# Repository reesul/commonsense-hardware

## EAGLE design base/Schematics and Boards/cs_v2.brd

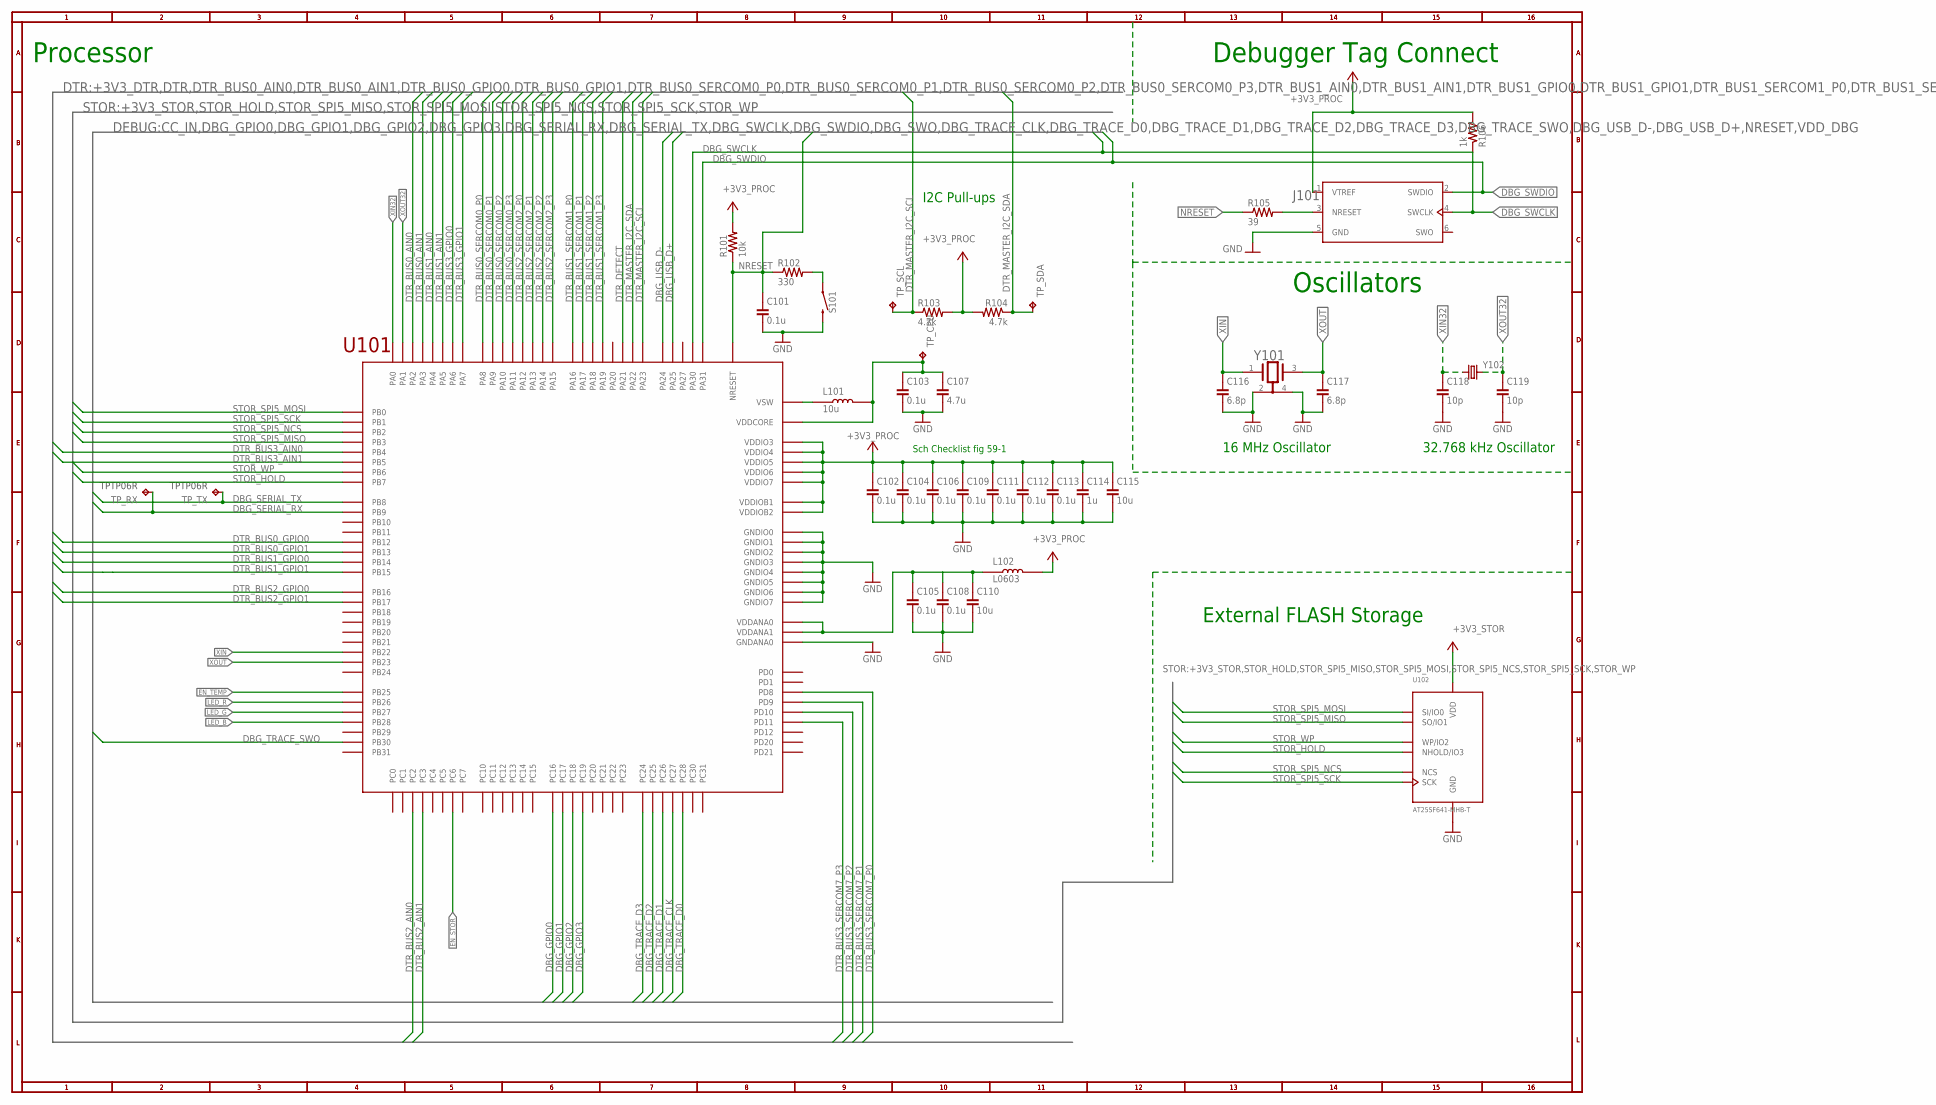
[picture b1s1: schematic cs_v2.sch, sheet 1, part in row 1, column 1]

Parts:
C101, C102, C103, C104, C105, C106, C108, C109, C111, C112, C113: 0.1u; C0402; VOLTAGE 10V; PART_NO C0402C104K8RACTU
C107: 4.7u; C0805; VOLTAGE 10V; PART_NO C0805C475K8RACTU
C110, C115: 10u; C0805; VOLTAGE 10V; PART_NO C0805C106M8RACTU
C114: 1u; C0402; VOLTAGE 10V; PART_NO C0402C105M8PACTU
C116, C117: 6.8p; C0402; PART_NO C0402C689D8GAC7867
C118, C119: 10p; C0402; PART_NO C0402C100C8GACTU
J101: J-JTAG-CORTEX-NEEDLE6; 8.06.16_6-PIN_NEEDLE_ADAPTER_NO-LEGS
L101: 10u; IND_LQH3NPN; PART_NO LQH3NPN100NM0L
L102: L0603; PART_NO BLM18PG471SN1D
R101: 10k; R0402; PART_NO P10KJCT-ND
R102: 330; R0402; PART_NO ERJ-2GEJ331X
R103, R104: 4.7k; R0402; PART_NO ERJ-3GEYJ472V
R105: 39; R0402; PART_NO ERJ-2GEJ390X
R106: 1k; R0402; PART_NO ERJ-2GEJ102X
S101: SW_EVQ-P7L01P_SPST_RA; SW_EVQ-P7L01P
TP_CPU: TPTP06R; TP06R
TP_RX: TPTP06R; TP06R
TP_SCL: TPTP06R; TP06R
TP_SDA: TPTP06R; TP06R
TP_TX: TPTP06R; TP06R
U101: ATSAMD51; TFBGA120
U102: AT25SF641-MHB-T; 8-UDFN
Y101: 16M; XTAL_EPSON_TSX3225
Y102: ABS07-32.768KHZ-9-T; XTAL320X150X90

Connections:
+3V3_PROC: C102.1, C104.1, C106.1, C109.1, C111.1, C112.1, C113.1, C114.1, C115.1, J101.1 (VTREF), L102.2, R101.2, R103.2, R104.2, R106.2, U101.VDDIO3, U101.VDDIO4, U101.VDDIO5, U101.VDDIO6, U101.VDDIO7, U101.VDDIOB1, U101.VDDIOB2; also elsewhere on the board
+3V3_STOR: U102.8 (VDD); also elsewhere on the board
DBG_GPIO0: U101.PC16; also elsewhere on the board
DBG_GPIO1: U101.PC17; also elsewhere on the board
DBG_GPIO2: U101.PC18; also elsewhere on the board
DBG_GPIO3: U101.PC19; also elsewhere on the board
DBG_SERIAL_RX: TP_RX.TP, U101.PB09 (PB9); also elsewhere on the board
DBG_SERIAL_TX: TP_TX.TP, U101.PB08 (PB8); also elsewhere on the board
DBG_SWCLK: J101.4 (SWCLK), R106.1, U101.PA30; also elsewhere on the board
DBG_SWDIO: J101.2 (SWDIO), U101.PA31; also elsewhere on the board
DBG_TRACE_CLK: U101.PC27; also elsewhere on the board
DBG_TRACE_D0: U101.PC28; also elsewhere on the board
DBG_TRACE_D1: U101.PC26; also elsewhere on the board
DBG_TRACE_D2: U101.PC25; also elsewhere on the board
DBG_TRACE_D3: U101.PC24; also elsewhere on the board
DBG_TRACE_SWO: U101.PB30; also elsewhere on the board
DBG_USB_D+: U101.PA25; also elsewhere on the board
DBG_USB_D-: U101.PA24; also elsewhere on the board
DTR_BUS0_AIN0: U101.PA02 (PA2); also elsewhere on the board
DTR_BUS0_AIN1: U101.PA03 (PA3); also elsewhere on the board
DTR_BUS0_GPIO0: U101.PB12; also elsewhere on the board
DTR_BUS0_GPIO1: U101.PB13; also elsewhere on the board
DTR_BUS0_SERCOM0_P0: U101.PA08 (PA8); also elsewhere on the board
DTR_BUS0_SERCOM0_P1: U101.PA09 (PA9); also elsewhere on the board
DTR_BUS0_SERCOM0_P2: U101.PA10; also elsewhere on the board
DTR_BUS0_SERCOM0_P3: U101.PA11; also elsewhere on the board
DTR_BUS1_AIN0: U101.PA04 (PA4); also elsewhere on the board
DTR_BUS1_AIN1: U101.PA05 (PA5); also elsewhere on the board
DTR_BUS1_GPIO0: U101.PB14; also elsewhere on the board
DTR_BUS1_GPIO1: U101.PB15; also elsewhere on the board
DTR_BUS1_SERCOM1_P0: U101.PA16; also elsewhere on the board
DTR_BUS1_SERCOM1_P1: U101.PA17; also elsewhere on the board
DTR_BUS1_SERCOM1_P2: U101.PA18; also elsewhere on the board
DTR_BUS1_SERCOM1_P3: U101.PA19; also elsewhere on the board
DTR_BUS2_AIN0: U101.PC02 (PC2); also elsewhere on the board
DTR_BUS2_AIN1: U101.PC03 (PC3); also elsewhere on the board
DTR_BUS2_GPIO0: U101.PB16; also elsewhere on the board
DTR_BUS2_GPIO1: U101.PB17; also elsewhere on the board
DTR_BUS2_SERCOM2_P0: U101.PA12; also elsewhere on the board
DTR_BUS2_SERCOM2_P1: U101.PA13; also elsewhere on the board
DTR_BUS2_SERCOM2_P2: U101.PA14; also elsewhere on the board
DTR_BUS2_SERCOM2_P3: U101.PA15; also elsewhere on the board
DTR_BUS3_AIN0: U101.PB04 (PB4); also elsewhere on the board
DTR_BUS3_AIN1: U101.PB05 (PB5); also elsewhere on the board
DTR_BUS3_GPIO0: U101.PA06 (PA6); also elsewhere on the board
DTR_BUS3_GPIO1: U101.PA07 (PA7); also elsewhere on the board
DTR_BUS3_SERCOM7_P0: U101.PD08 (PD8); also elsewhere on the board
DTR_BUS3_SERCOM7_P1: U101.PD09 (PD9); also elsewhere on the board
DTR_BUS3_SERCOM7_P2: U101.PD10; also elsewhere on the board
DTR_BUS3_SERCOM7_P3: U101.PD11; also elsewhere on the board
DTR_DETECT: U101.PA21; also elsewhere on the board
DTR_MASTER_I2C_SCL: R103.1, TP_SCL.TP, U101.PA23; also elsewhere on the board
DTR_MASTER_I2C_SDA: R104.1, TP_SDA.TP, U101.PA22; also elsewhere on the board
EN_STOR: U101.PC06 (PC6); also elsewhere on the board
EN_TEMP: U101.PB25; also elsewhere on the board
GND: C101.2, C102.2, C103.2, C104.2, C105.2, C106.2, C107.2, C108.2, C109.2, C110.2, C111.2, C112.2, C113.2, C114.2, C115.2, C116.2, C117.2, C118.2, C119.2, J101.5 (GND), S101.2_1 (2), S101.2_2 (2), U101.GNDANA0, U101.GNDIO0, U101.GNDIO1, U101.GNDIO2, U101.GNDIO3, U101.GNDIO4, U101.GNDIO5, U101.GNDIO6, U101.GNDIO7, U102.4 (GND), U102.9 (GND), Y101.2 (1_GND), Y101.4 (2_GND); also elsewhere on the board
JTAG_NRESET: J101.3 (NRESET), R105.2
LED_B: U101.PB28; also elsewhere on the board
LED_G: U101.PB27; also elsewhere on the board
LED_R: U101.PB26; also elsewhere on the board
unnamed: R102.2, S101.1_1 (1), S101.1_2 (1)
NRESET: C101.1, R101.1, R102.1, R105.1, U101.NRESET; also elsewhere on the board
STOR_HOLD: U101.PB07 (PB7), U102.7 (NHOLD/IO3)
STOR_SPI5_MISO: U101.PB03 (PB3), U102.2 (SO/IO1)
STOR_SPI5_MOSI: U101.PB00 (PB0), U102.5 (SI/IO0)
STOR_SPI5_NCS: U101.PB02 (PB2), U102.1 (NCS)
STOR_SPI5_SCK: U101.PB01 (PB1), U102.6 (SCK)
STOR_WP: U101.PB06 (PB6), U102.3 (WP/IO2)
VDDANA: C105.1, C108.1, C110.1, L102.1, U101.VDDANA0, U101.VDDANA1
VDDCORE: C103.1, C107.1, L101.2, L101.P$2, TP_CPU.TP, U101.VDDCORE
VSW: L101.1, L101.P$1, U101.VSW
XIN: C116.1, U101.PB22, Y101.1
XIN32: C118.1, U101.PA00 (PA0), Y102.1
XOUT: C117.1, U101.PB23, Y101.3
XOUT32: C119.1, U101.PA01 (PA1), Y102.2

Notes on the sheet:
Sch Checklist fig 59-1
Oscillators
16 MHz Oscillator
32.768 kHz Oscillator
Processor
Debugger Tag Connect
I2C Pull-ups
External FLASH Storage

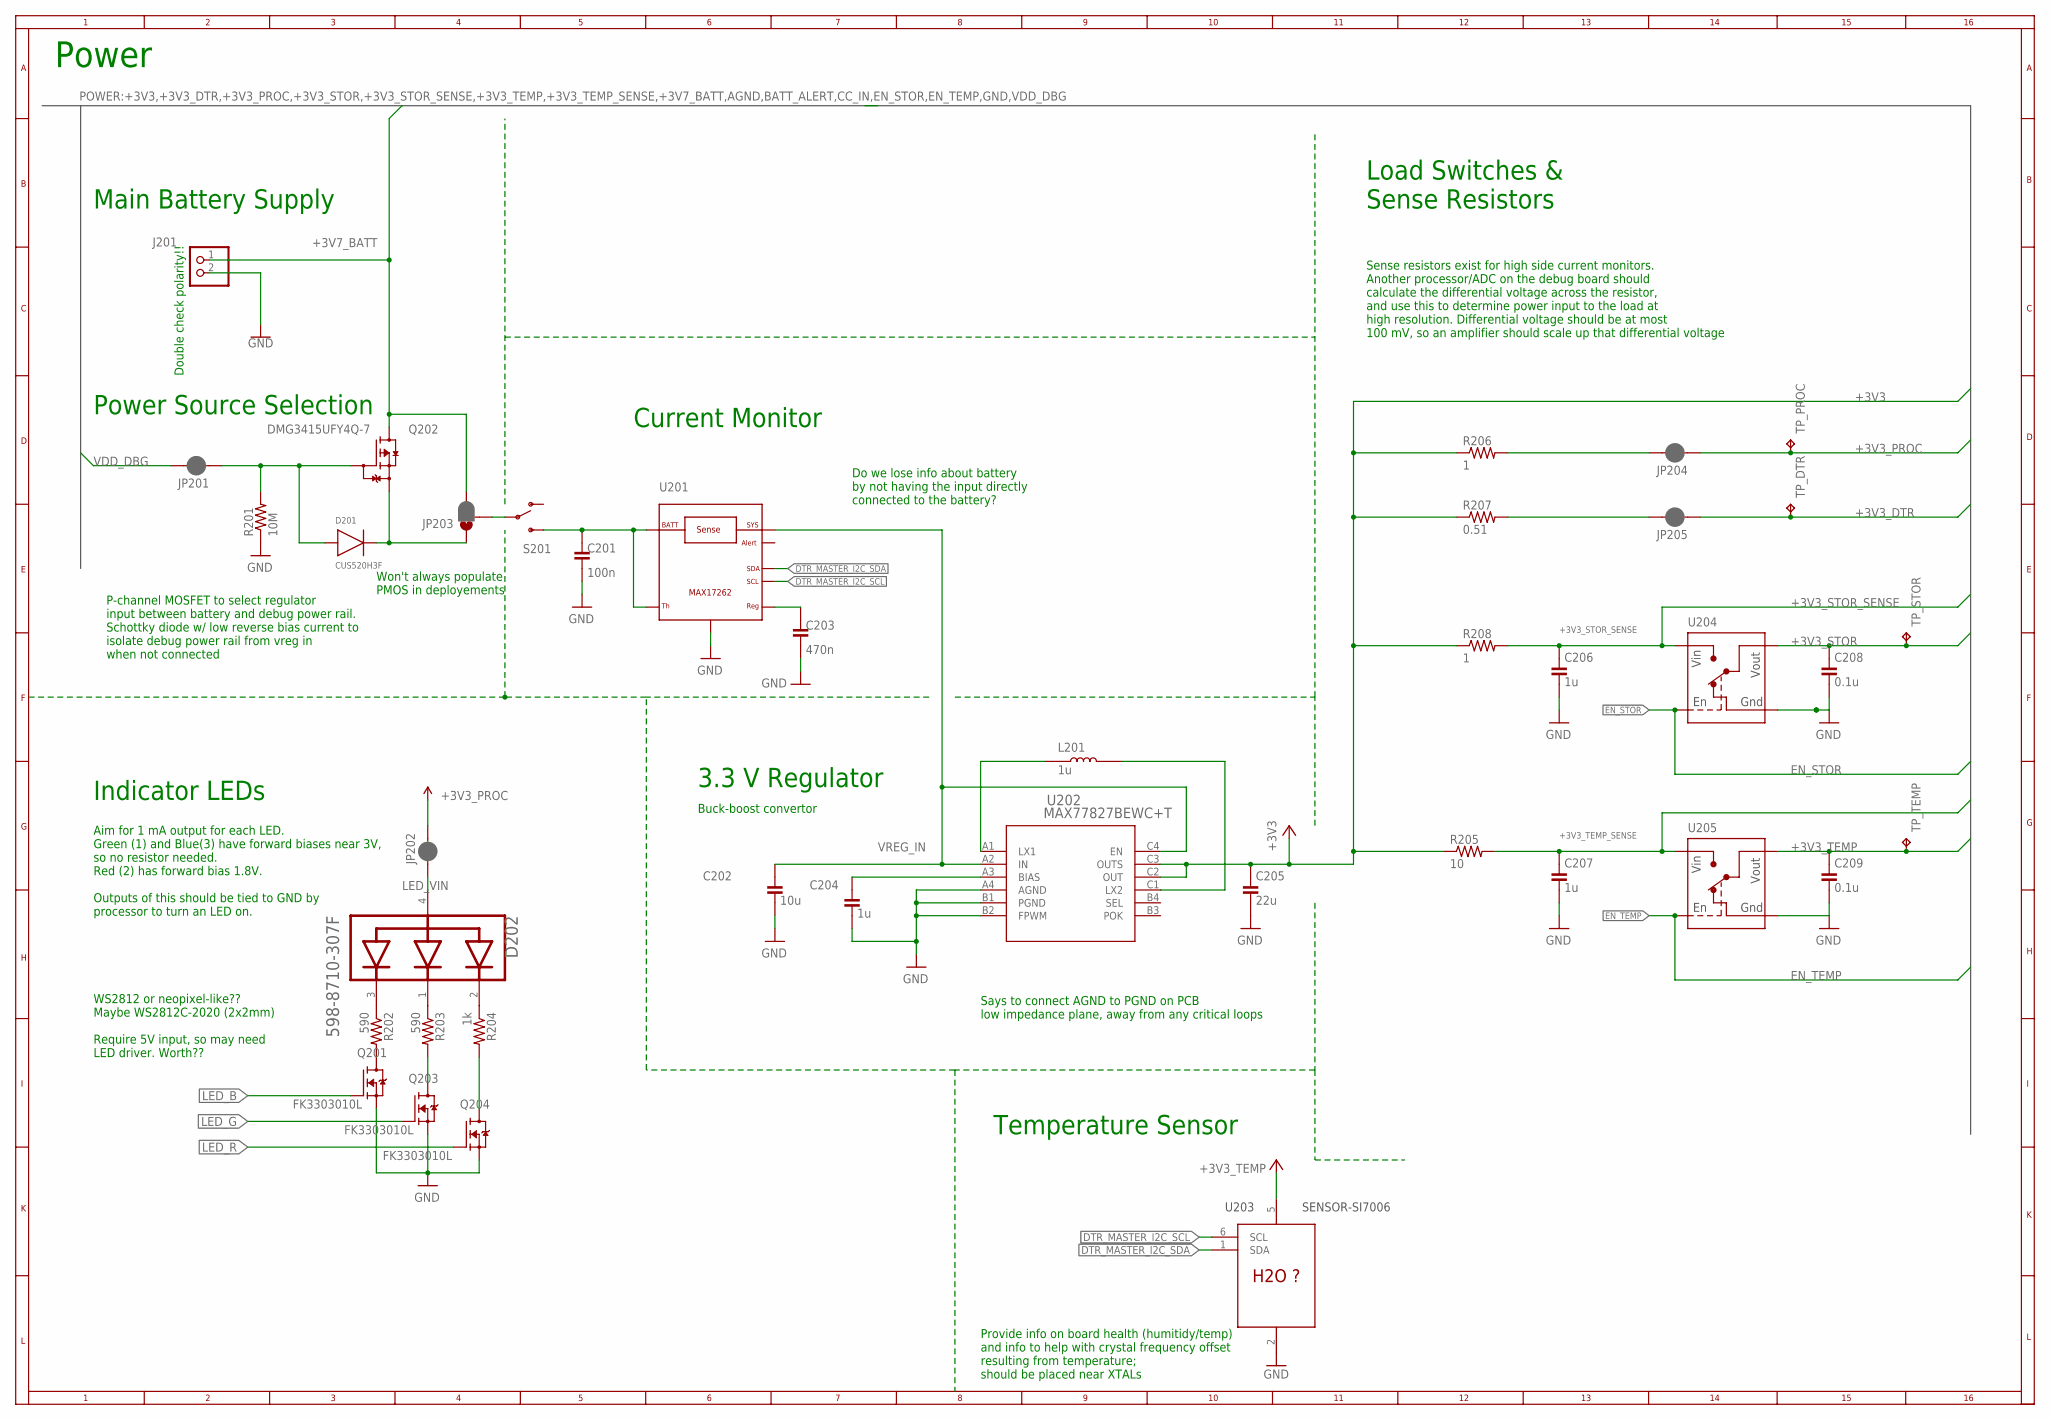
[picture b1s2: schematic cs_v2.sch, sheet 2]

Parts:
C201: 100n; C0402
C202: 10u; C0603; VOLTAGE 10V; PART_NO C0603C106M8PAC7867
C203: 470n; C0402
C204: 1u; C0402; VOLTAGE 10V; PART_NO C0402C105K8PACTU
C205: 22u; C0805; VOLTAGE 10V; PART_NO C0805C226M8PAC7800
C206, C207: 1u; C0402; VOLTAGE 10V; PART_NO C0402C105M8PACTU
C208, C209: 0.1u; C0402; VOLTAGE 10V; PART_NO C0402C104K8RACTU
D201: CUS520H3F
D202: DIALIGHT_RGBLED_598-8710-307FDIALIGHT_598-8710-30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; DIALIGHT_0606_598-8710-307F_0; PART_NO 598-8710-307F
J201: J-JST2-SMT-RA; JST-PH-2-SMT-RA; PART_NO SM02B-SRSS-TB
JP201, JP202, JP204, JP205: JUMPER-SMT_2_NC_PASTE_NO-SILK; SMT-JUMPER_2_NC_PASTE_NO-SILK
JP203: JUMPER-SMT_3_1-NC_PASTE_NO-SILK; SMT-JUMPER_3_1-NC_PASTE_NO-SILK
L201: 1u; L1008
Q201, Q203, Q204: FK3303010L; SSSMINI3
Q202: DMG3415UFY4Q-7; SOT23-3; PART_NO DMG3415UFY4Q-7
R201: 10M; R0402; PART_NO ERJ-2GEJ106X
R202, R203: 590; R0402; PART_NO ERJ-2RKF5900X
R204: 1k; R0402; PART_NO ERA-2AED102X
R205: 10; R0603; PART_NO ERA-3AHD100V
R206, R208: 1; R0603; PART_NO ERJ-3RQF1R0V
R207: 0.51; R0603; PART_NO ERJ-3BQFR51V
S201: SLIDESWITCH-SPDT-SMD-RIGHT-ANGLE; SWITCH_SPST_SMD_A; PART_NO CUS-12TB
TP_DTR: TPTP06R; TP06R
TP_PROC: TPTP06R; TP06R
TP_STOR: TPTP06R; TP06R
TP_TEMP: TPTP06R; TP06R
U201: COULOMB-MAX17262; BGA9N40P3X3_144X146X69N
U202: MAX77827BEWC+T; 12-WLP
U203: SENSOR-SI7006; DFN-06
U204, U205: LOADSWITCH-MIC94164; WLCSP6_2X3; PART_NO MIC94162YCS-TR

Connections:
+3V3: C205.1, R205.1, R206.1, R207.1, R208.1, U202.C2 (OUT), U202.C3 (OUTS); also elsewhere on the board
+3V3_DTR: JP205.1, TP_DTR.TP; also elsewhere on the board
+3V3_DTR_SENSE: JP205.2, R207.2
+3V3_PROC: JP202.2, JP204.1, TP_PROC.TP; also elsewhere on the board
+3V3_PROC_SENSE: JP204.2, R206.2
+3V3_STOR: C208.1, TP_STOR.TP, U204.A1 (VOUT), U204.B1 (VOUT); also elsewhere on the board
+3V3_STOR_SENSE: C206.1, R208.2, U204.A2 (VIN), U204.B2 (VIN); also elsewhere on the board
+3V3_TEMP: C209.1, TP_TEMP.TP, U203.5 (V), U205.A1 (VOUT), U205.B1 (VOUT)
+3V3_TEMP_SENSE: C207.1, R205.2, U205.A2 (VIN), U205.B2 (VIN); also elsewhere on the board
+3V7_BATT: J201.1 (2), JP203.3, Q202.3 (D); also elsewhere on the board
CC_IN: C201.1, S201.3 (S), U201.A1 (TH), U201.A2 (BATT)
DTR_MASTER_I2C_SCL: U201.B1 (SCL), U203.6 (SCL); also elsewhere on the board
DTR_MASTER_I2C_SDA: U201.C1 (SDA), U203.1 (SDA); also elsewhere on the board
EN_STOR: U204.C2 (ENABLE); also elsewhere on the board
EN_TEMP: U205.C2 (ENABLE); also elsewhere on the board
GND: C201.2, C202.2, C203.2, C204.2, C205.2, C206.2, C207.2, C208.2, C209.2, J201.2 (1), Q201.1 (S), Q203.1 (S), Q204.1 (S), R201.1, U201.C3 (GND), U202.A4 (AGND), U202.B1 (PGND), U202.B2 (FPWM), U203.2 (GND), U204.C1 (GND), U205.C1 (GND); also elsewhere on the board
LED_B: Q201.3 (G); also elsewhere on the board
LED_G: Q203.3 (G); also elsewhere on the board
LED_R: Q204.3 (G); also elsewhere on the board
LED_VIN: D202.4 (COMMON_ANODE), JP202.1
unnamed: D202.3 (BLUE_CATHODE), R202.1
unnamed: D202.1 (GREEN_CATHODE), R203.1
unnamed: C203.1, U201.C2 (REG)
unnamed: D202.2 (RED_CATHODE), R204.1
unnamed: Q201.2 (D), R202.2
unnamed: Q203.2 (D), R203.2
unnamed: Q204.2 (D), R204.2
VDD_DBG: JP201.2; also elsewhere on the board
VDD_DBG_JMP: D201.P, JP201.1, Q202.1 (G), R201.2
VDD_SW: D201.N, JP203.1, Q202.2 (S)
VDD_SW_IN: JP203.2, S201.2
VREG_BIAS: C204.1, U202.A3 (BIAS)
VREG_IN: C202.1, U201.B3 (SYS), U202.A2 (IN), U202.C4 (EN)
VREG_LX1: L201.1, U202.A1 (LX1)
VREG_LX2: L201.2, U202.C1 (LX2)

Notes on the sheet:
Double check polarity!!
Sense resistors exist for high side current monitors. Another processor/ADC on the debug board should calculate the differential voltage across the resistor, and use this to determine power input to the load at high resolution. Differential voltage should be at most 100 mV, so an amplifier should s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
Power
P-channel MOSFET to select regulator input between battery and debug power rail. Schottky diode w/ low reverse bias current to isolate debug power rail from vreg in when not connected
3.3 V Regulator
Power Source Selection
Main Battery Supply
Load Switches & Sense Resistors
Buck-boost convertor
Aim for 1 mA output for each LED. Green (1) and Blue(3) have forward biases near 3V, so no resistor needed. Red (2) has forward bias 1.8V. Outputs of this should be tied to GND by processor to turn an LED on.
Indicator LEDs
WS2812 or neopixel-like?? Maybe WS2812C-2020 (2x2mm) Require 5V input, so may need LED driver. Worth??
Temperature Sensor
Says to connect AGND to PGND on PCB low impedance plane, away from any critical loops
Provide info on board health (humitidy/temp) and info to help with crystal frequency offset resulting from temperature; should be placed near XTALs
Current Monitor
Do we lose info about battery by not having the input directly connected to the battery?
Won't always populate PMOS in deployements

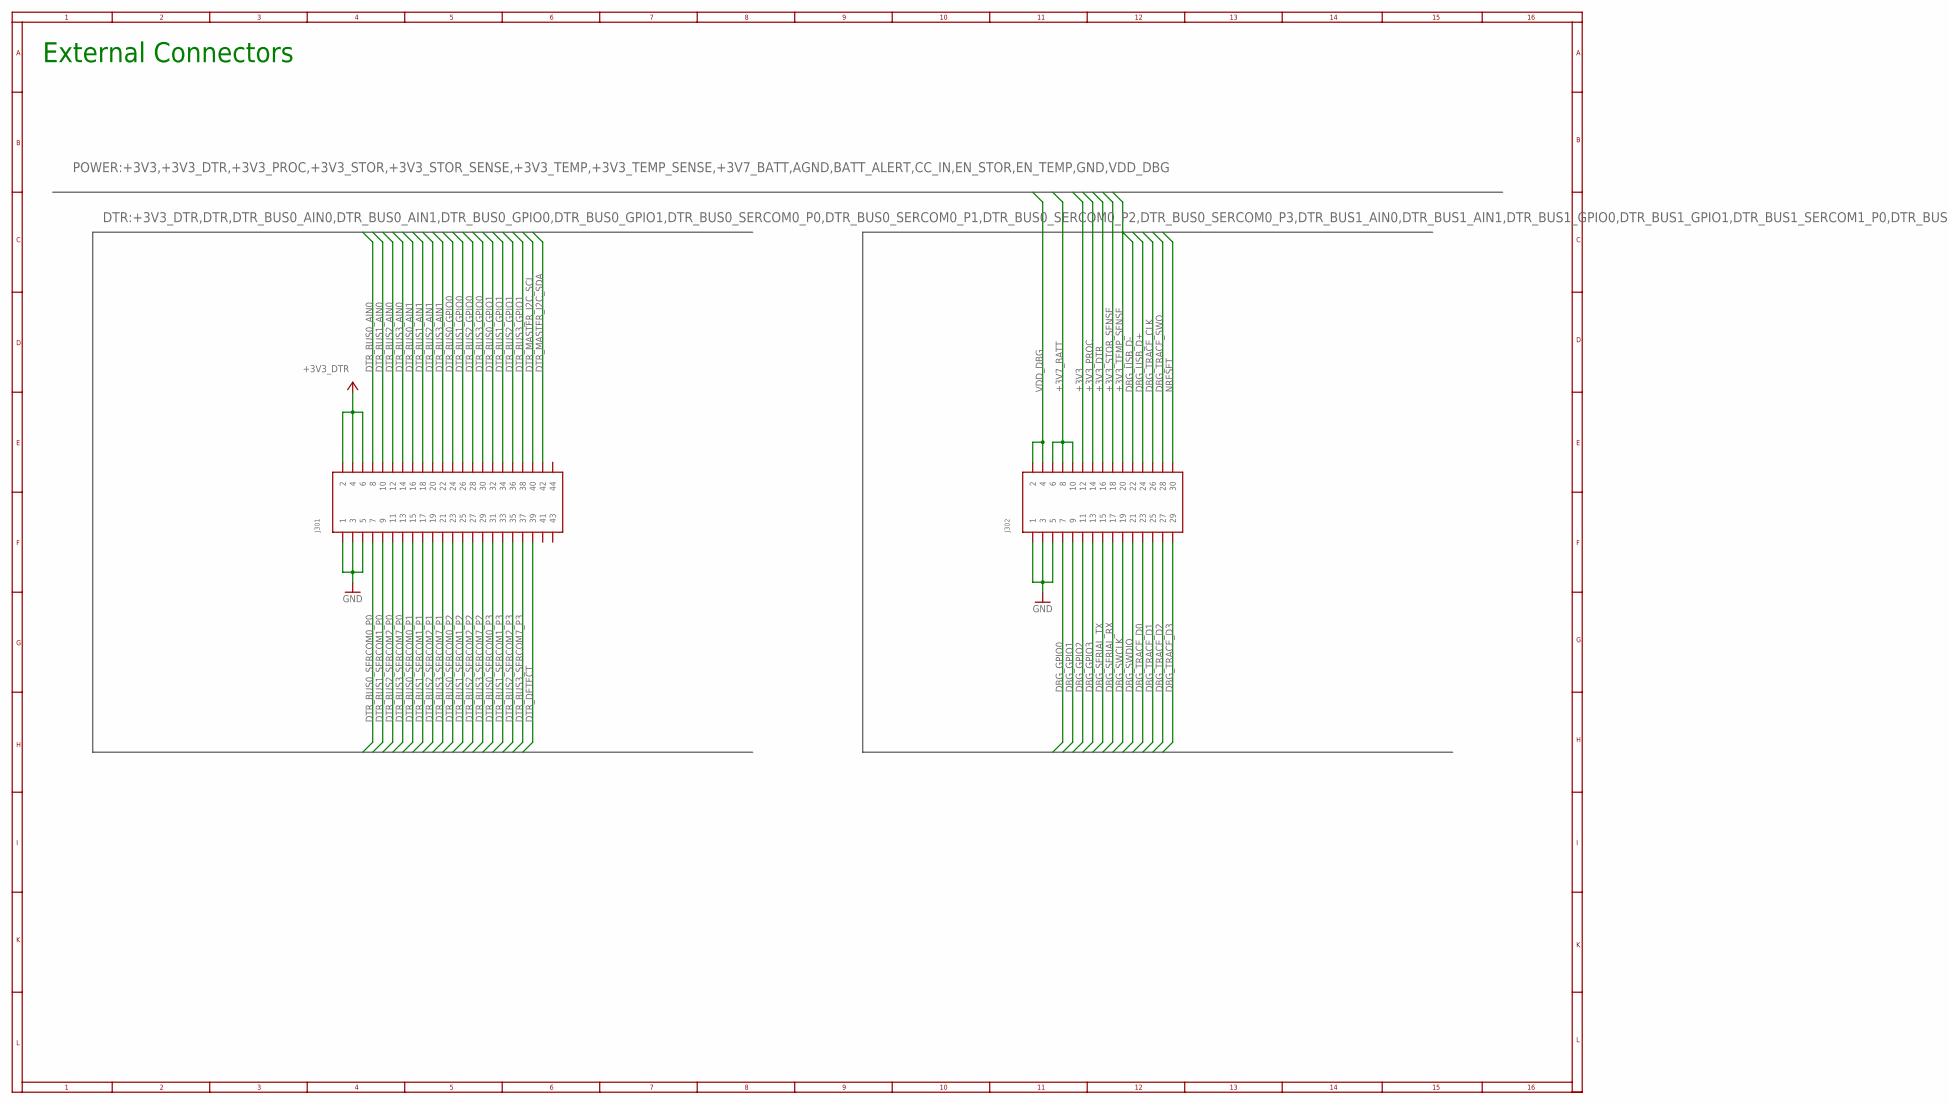
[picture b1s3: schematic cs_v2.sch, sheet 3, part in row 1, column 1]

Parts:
J301: HIROSE-DF40_44-PIN_CONNECTORS-RECEPTACLE; HRS_DF40HC(3.0)-44DS-0.4V(51)
J302: HIROSE-DF40_30-PIN_CONNECTORS-RECEPTACLE; HRS_DF40HC(3.0)-30DS-0.4V(51)

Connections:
+3V3: J302.12; also elsewhere on the board
+3V3_DTR: J301.2, J301.4, J301.6, J302.16; also elsewhere on the board
+3V3_PROC: J302.14; also elsewhere on the board
+3V3_STOR_SENSE: J302.18; also elsewhere on the board
+3V3_TEMP_SENSE: J302.20; also elsewhere on the board
+3V7_BATT: J302.6, J302.8, J302.10; also elsewhere on the board
DBG_GPIO0: J302.7; also elsewhere on the board
DBG_GPIO1: J302.9; also elsewhere on the board
DBG_GPIO2: J302.11; also elsewhere on the board
DBG_GPIO3: J302.13; also elsewhere on the board
DBG_SERIAL_RX: J302.17; also elsewhere on the board
DBG_SERIAL_TX: J302.15; also elsewhere on the board
DBG_SWCLK: J302.19; also elsewhere on the board
DBG_SWDIO: J302.21; also elsewhere on the board
DBG_TRACE_CLK: J302.26; also elsewhere on the board
DBG_TRACE_D0: J302.23; also elsewhere on the board
DBG_TRACE_D1: J302.25; also elsewhere on the board
DBG_TRACE_D2: J302.27; also elsewhere on the board
DBG_TRACE_D3: J302.29; also elsewhere on the board
DBG_TRACE_SWO: J302.28; also elsewhere on the board
DBG_USB_D+: J302.24; also elsewhere on the board
DBG_USB_D-: J302.22; also elsewhere on the board
DTR_BUS0_AIN0: J301.8; also elsewhere on the board
DTR_BUS0_AIN1: J301.16; also elsewhere on the board
DTR_BUS0_GPIO0: J301.24; also elsewhere on the board
DTR_BUS0_GPIO1: J301.32; also elsewhere on the board
DTR_BUS0_SERCOM0_P0: J301.7; also elsewhere on the board
DTR_BUS0_SERCOM0_P1: J301.15; also elsewhere on the board
DTR_BUS0_SERCOM0_P2: J301.23; also elsewhere on the board
DTR_BUS0_SERCOM0_P3: J301.31; also elsewhere on the board
DTR_BUS1_AIN0: J301.10; also elsewhere on the board
DTR_BUS1_AIN1: J301.18; also elsewhere on the board
DTR_BUS1_GPIO0: J301.26; also elsewhere on the board
DTR_BUS1_GPIO1: J301.34; also elsewhere on the board
DTR_BUS1_SERCOM1_P0: J301.9; also elsewhere on the board
DTR_BUS1_SERCOM1_P1: J301.17; also elsewhere on the board
DTR_BUS1_SERCOM1_P2: J301.25; also elsewhere on the board
DTR_BUS1_SERCOM1_P3: J301.33; also elsewhere on the board
DTR_BUS2_AIN0: J301.12; also elsewhere on the board
DTR_BUS2_AIN1: J301.20; also elsewhere on the board
DTR_BUS2_GPIO0: J301.28; also elsewhere on the board
DTR_BUS2_GPIO1: J301.36; also elsewhere on the board
DTR_BUS2_SERCOM2_P0: J301.11; also elsewhere on the board
DTR_BUS2_SERCOM2_P1: J301.19; also elsewhere on the board
DTR_BUS2_SERCOM2_P2: J301.27; also elsewhere on the board
DTR_BUS2_SERCOM2_P3: J301.35; also elsewhere on the board
DTR_BUS3_AIN0: J301.14; also elsewhere on the board
DTR_BUS3_AIN1: J301.22; also elsewhere on the board
DTR_BUS3_GPIO0: J301.30; also elsewhere on the board
DTR_BUS3_GPIO1: J301.38; also elsewhere on the board
DTR_BUS3_SERCOM7_P0: J301.13; also elsewhere on the board
DTR_BUS3_SERCOM7_P1: J301.21; also elsewhere on the board
DTR_BUS3_SERCOM7_P2: J301.29; also elsewhere on the board
DTR_BUS3_SERCOM7_P3: J301.37; also elsewhere on the board
DTR_DETECT: J301.39; also elsewhere on the board
DTR_MASTER_I2C_SCL: J301.40; also elsewhere on the board
DTR_MASTER_I2C_SDA: J301.42; also elsewhere on the board
GND: J301.1, J301.3, J301.5, J302.1, J302.3, J302.5; also elsewhere on the board
NRESET: J302.30; also elsewhere on the board
VDD_DBG: J302.2, J302.4; also elsewhere on the board

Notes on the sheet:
External Connectors

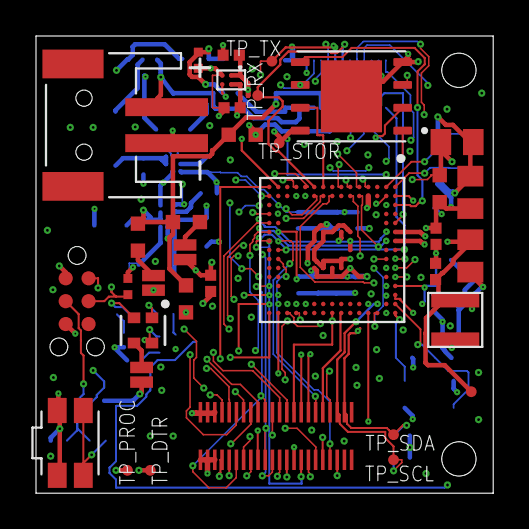
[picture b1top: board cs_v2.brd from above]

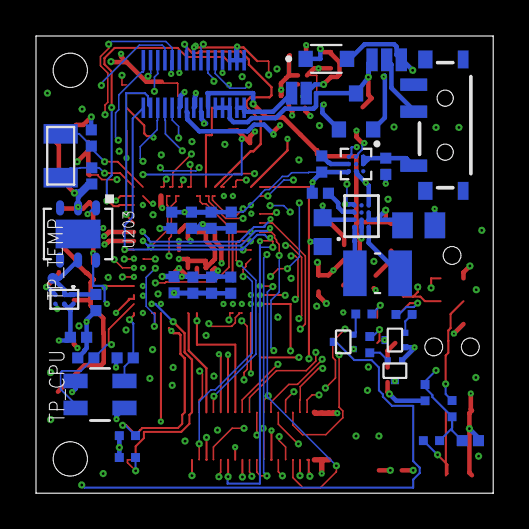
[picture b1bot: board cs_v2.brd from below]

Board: 8 copper layers, 25.4 x 25.4 mm, 80 parts (45 on the bottom side), 100 nets.

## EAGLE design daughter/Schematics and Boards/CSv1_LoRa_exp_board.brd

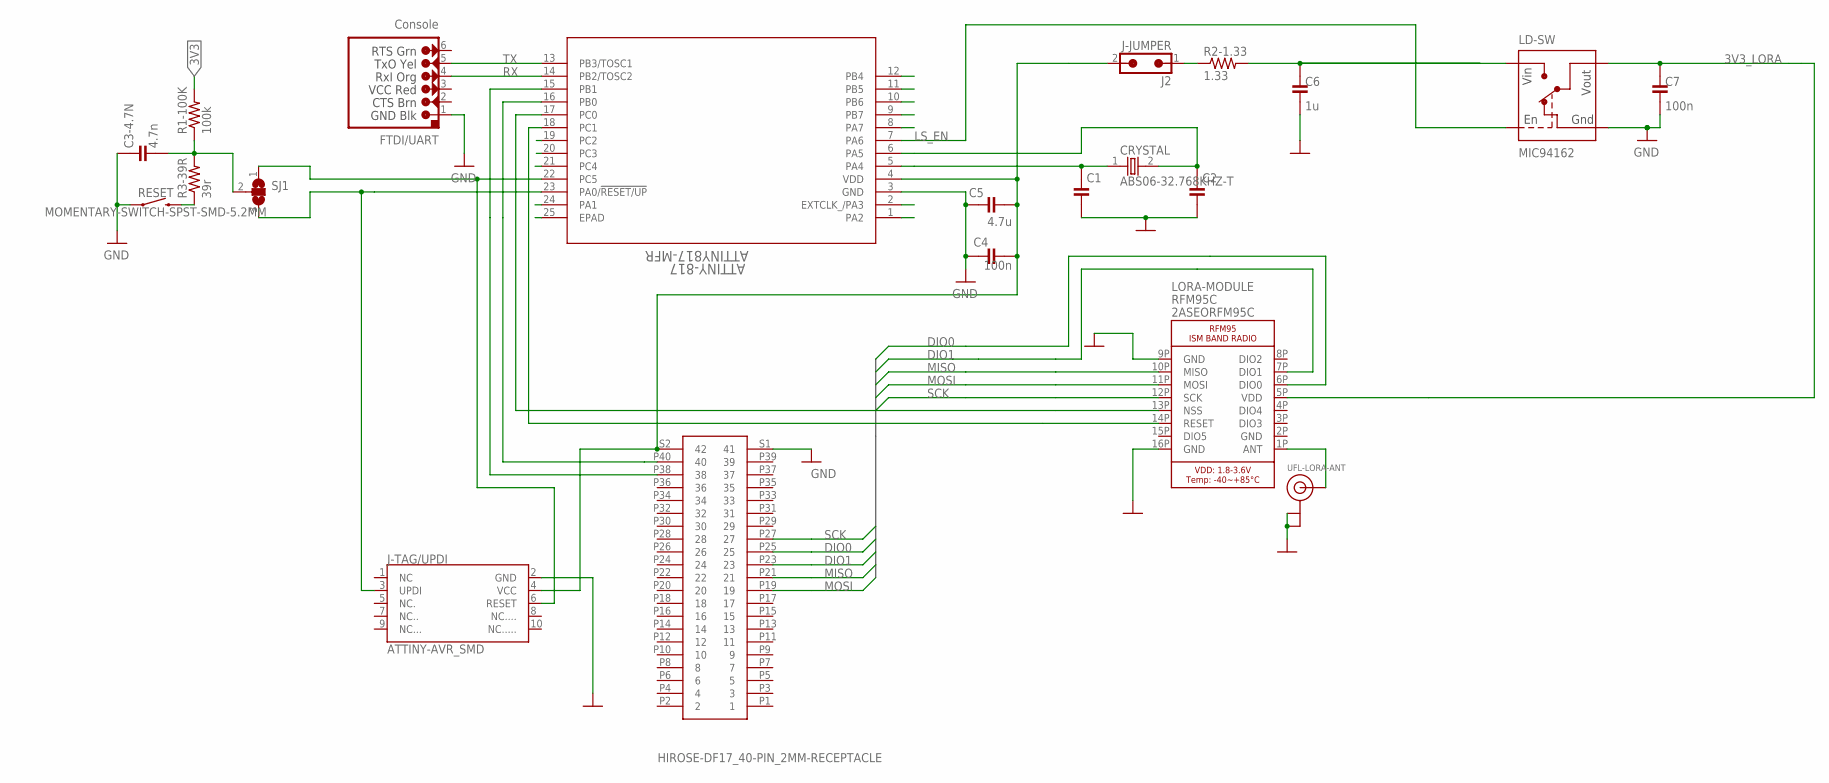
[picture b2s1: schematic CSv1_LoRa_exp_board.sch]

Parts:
ATTINY-817: ATTINY817-MFR; QFN24_4X4MC
C1, C2: C-0402; C0402
C3-4.7N: 4.7n; C0603
C4: 100n; C0402; PARTNO CC0402KRX5R5BB105
C5: 4.7u; C0402; PARTNO CC0402KRX5R5BB105
C6: 1u; C0402; PARTNO CC0402KRX5R5BB105
C7: 100n; C0402; PARTNO CC0402KRX5R5BB104
CRYSTAL: ABS06-32.768KHZ-T; XTAL_ABS06-32.768KHZ-T
FTDI/UART: J-SERIAL-PORT; HEADER-1X6
J1: HIROSE-DF17_40-PIN_2MM-RECEPTACLE; HRS_DF17-40PIN-PLUG
J2: J-JUMPER; HEADER-1X2
J-TAG/UPDI: ATTINY-AVR_SMD; ATTINY_AVR
LD-SW: LOADSWITCH-MIC94162; WLCSP6_2X3
LORA-MODULE: RFM95C; RFM-MOD
R1-100K: 100k; R0603
R2-1.33: 1.33; R0603; PARTNO CRCW06031R33FKEA
R3-39R: 39r; R0603
RESET: MOMENTARY-SWITCH-SPST-SMD-5.2MM; TACTILE_SWITCH_SMD_5.2MM
SJ1: SJ2WW; SJ_2W
UFL-LORA-ANT: J-U.FL; U.FL

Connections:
3V3: ATTINY-817.4 (VDD), C4.2, C5.2, J1.S2 (42), J2.2, J-TAG/UPDI.4 (VCC), R1-100K.2
3V3_LORA: C7.1, LD-SW.A1 (VOUT), LD-SW.B1 (VOUT), LORA-MODULE.5P (VDD)
3V_LD_SW: C6.1, LD-SW.A2 (VIN), LD-SW.B2 (VIN), R2-1.33.2
DIO0: J1.P25 (25), LORA-MODULE.6P (DIO0)
DIO1: J1.P23 (23), LORA-MODULE.7P (DIO1)
EPAD: ATTINY-817.25 (EPAD)
GND: ATTINY-817.3 (GND), C1.2, C2.2, C3-4.7N.1, C4.1, C5.1, C6.2, C7.2, FTDI/UART.1 (GND), J1.S1 (41), J-TAG/UPDI.2 (GND), LD-SW.C1 (GND), LORA-MODULE.2P (GND), LORA-MODULE.9P (GND), LORA-MODULE.16P (GND), RESET.1, UFL-LORA-ANT.1 (GND), UFL-LORA-ANT.2 (GND)
LORA_JMP1: J2.1, R2-1.33.1
LS_EN: ATTINY-817.7 (PA6), LD-SW.C2 (ENABLE)
MISO: J1.P21 (21), LORA-MODULE.10P (MISO)
MOSI: J1.P19 (19), LORA-MODULE.11P (MOSI)
unnamed: LORA-MODULE.1P (ANT), UFL-LORA-ANT.3 (SIGNAL)
unnamed: R3-39R.1, RESET.3 (2)
unnamed: C3-4.7N.2, R1-100K.1, R3-39R.2, SJ1.2
PA0: ATTINY-817.23 (PA0/!RESET/UP), J-TAG/UPDI.3 (UPDI), SJ1.3
PA1: ATTINY-817.24 (PA1)
PA2: ATTINY-817.1 (PA2)
PA3: ATTINY-817.2 (EXTCLK_/PA3)
PA4: ATTINY-817.5 (PA4), C1.1, CRYSTAL.1
PA5: ATTINY-817.6 (PA5), C2.1, CRYSTAL.2
PA7: ATTINY-817.8 (PA7)
PB0: ATTINY-817.16 (PB0), J1.P40 (40)
PB4: ATTINY-817.12 (PB4)
PB5: ATTINY-817.11 (PB5)
PB6: ATTINY-817.10 (PB6)
PB7: ATTINY-817.9 (PB7)
PC0: ATTINY-817.17 (PC0), LORA-MODULE.13P (NSS)
PC1: ATTINY-817.18 (PC1), LORA-MODULE.14P (RESET)
PC2: ATTINY-817.19 (PC2)
PC3: ATTINY-817.20 (PC3)
PC4: ATTINY-817.21 (PC4)
PC5: ATTINY-817.22 (PC5), J-TAG/UPDI.6 (RESET), SJ1.1
RX: ATTINY-817.14 (PB2/TOSC2), FTDI/UART.4 (RX-I)
SCK: J1.P27 (27), LORA-MODULE.12P (SCK)
SDA: ATTINY-817.15 (PB1), J1.P38 (38)
TX: ATTINY-817.13 (PB3/TOSC1), FTDI/UART.5 (TX-O)

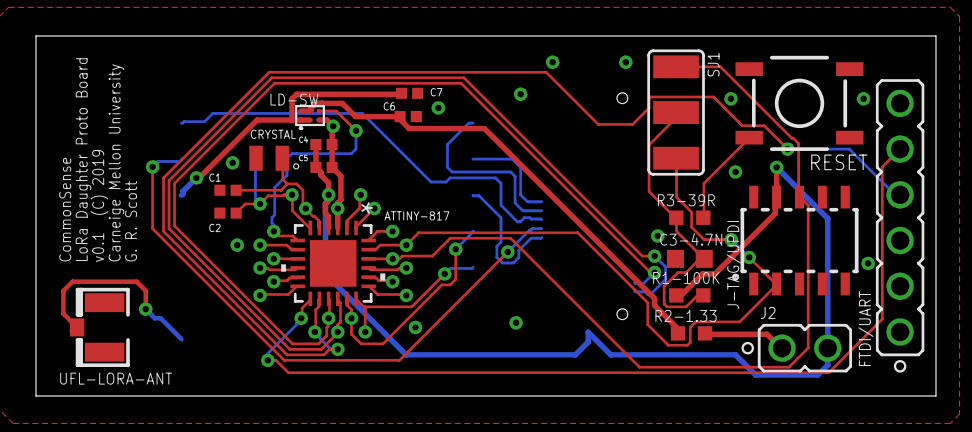
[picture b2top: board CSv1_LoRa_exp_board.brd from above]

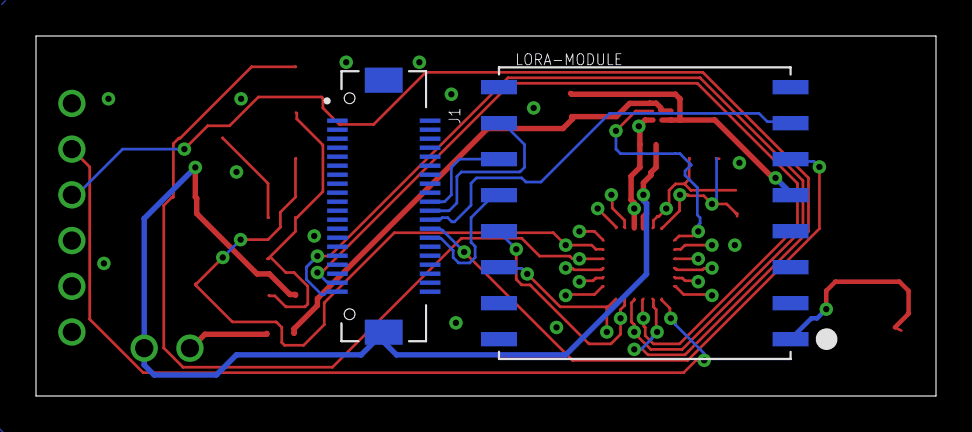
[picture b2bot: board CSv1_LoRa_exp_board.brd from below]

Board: 2 copper layers, 50.0 x 20.0 mm, 21 parts (2 on the bottom side), 24 nets.

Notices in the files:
daughter/Schematics and Boards/CSv1_LoRa_exp_board.brd:
v0.1  (C) 2019
parts and their libraries:
Graphics: Copyright (c) 2004-2019 Bob Iannucci
Graphics: All rights reserved worldwide.
Oscillators: COPYRIGHT: Copyright (C) 2018 Accelerated Designs. All rights reserved
SparkFun-Jumpers: Licensing: Creative Commons ShareAlike 4.0 International - https://creativecommons.org/licenses/by-sa/4.0
